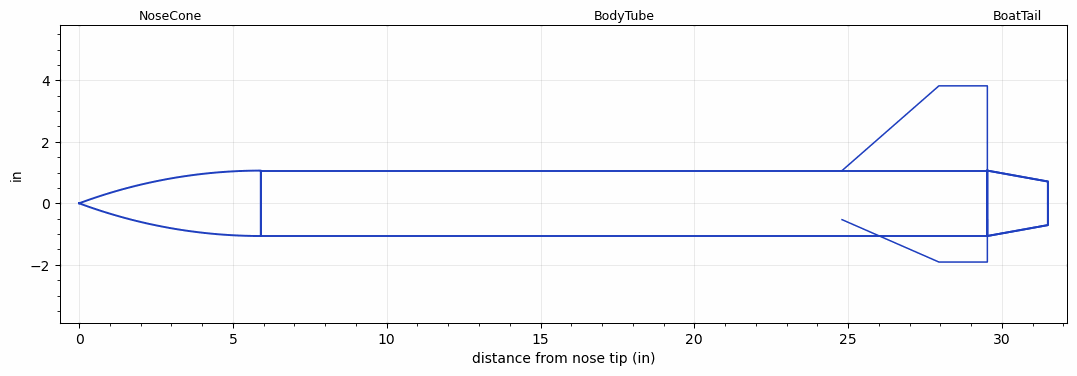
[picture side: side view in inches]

<RASAeroDocument>
 <FileVersion>2</FileVersion>
 <RocketDesign>
  <NoseCone>
   <Length>5.9055118</Length>
   <Diameter>2.1259843</Diameter>
   <Shape>Tangent Ogive</Shape>
   <Location>0</Location>
  </NoseCone>
  <BodyTube>
   <Length>23.622047</Length>
   <Diameter>2.1259843</Diameter>
   <RailGuideDiameter>0.39370079</RailGuideDiameter>
   <RailGuideHeight>0.39370079</RailGuideHeight>
   <Location>5.9055118</Location>
   <BoattailLength>1.9685039</BoattailLength>
   <BoattailRearDiameter>1.4173228</BoattailRearDiameter>
   <Fin>
    <Count>3</Count>
    <Chord>4.7244094</Chord>
    <Span>2.7559055</Span>
    <SweepDistance>3.1496063</SweepDistance>
    <TipChord>1.5748031</TipChord>
    <Thickness>0.11811024</Thickness>
    <Location>4.7244094</Location>
    <AirfoilSection>Square</AirfoilSection>
   </Fin>
  </BodyTube>
  <BoatTail>
   <Length>1.9685039</Length>
   <Diameter>2.1259843</Diameter>
   <RearDiameter>1.4173228</RearDiameter>
   <Location>29.527559</Location>
  </BoatTail>
  <Surface>Rough Camouflage Paint</Surface>
  <ModifiedBarrowman>False</ModifiedBarrowman>
  <Turbulence>False</Turbulence>
  <UseBooster1>False</UseBooster1>
  <UseBooster2>False</UseBooster2>
  <Comments>Exported by lo-fi-rocket from "r2-ogive-boattail".</Comments>
 </RocketDesign>
 <LaunchSite>
  <Altitude>0</Altitude>
  <Pressure>0</Pressure>
  <RodAngle>0</RodAngle>
  <RodLength>4.9212598</RodLength>
  <Temperature>59</Temperature>
  <WindSpeed>0</WindSpeed>
 </LaunchSite>
 <Recovery>
  <Altitude1>1000</Altitude1>
  <Altitude2>1000</Altitude2>
  <DeviceType1>Parachute</DeviceType1>
  <DeviceType2>None</DeviceType2>
  <Event1>True</Event1>
  <Event2>False</Event2>
  <Size1>17.716535</Size1>
  <Size2>0</Size2>
  <EventType1>Apogee</EventType1>
  <EventType2>None</EventType2>
  <CD1>0.8</CD1>
  <CD2>1.33</CD2>
 </Recovery>
 <SimulationList>
  <Simulation>
   <SustainerEngine>LF-G80NBT  (LoFi)</SustainerEngine>
   <SustainerLaunchWt>0.91378214</SustainerLaunchWt>
   <SustainerCG>19.07667</SustainerCG>
   <SustainerIgnitionDelay>0</SustainerIgnitionDelay>
   <Booster1SeparationDelay>0</Booster1SeparationDelay>
   <Booster1IgnitionDelay>0</Booster1IgnitionDelay>
   <IncludeBooster1>False</IncludeBooster1>
   <Booster2Delay>0</Booster2Delay>
   <IncludeBooster2>False</IncludeBooster2>
  </Simulation>
 </SimulationList>
</RASAeroDocument>
